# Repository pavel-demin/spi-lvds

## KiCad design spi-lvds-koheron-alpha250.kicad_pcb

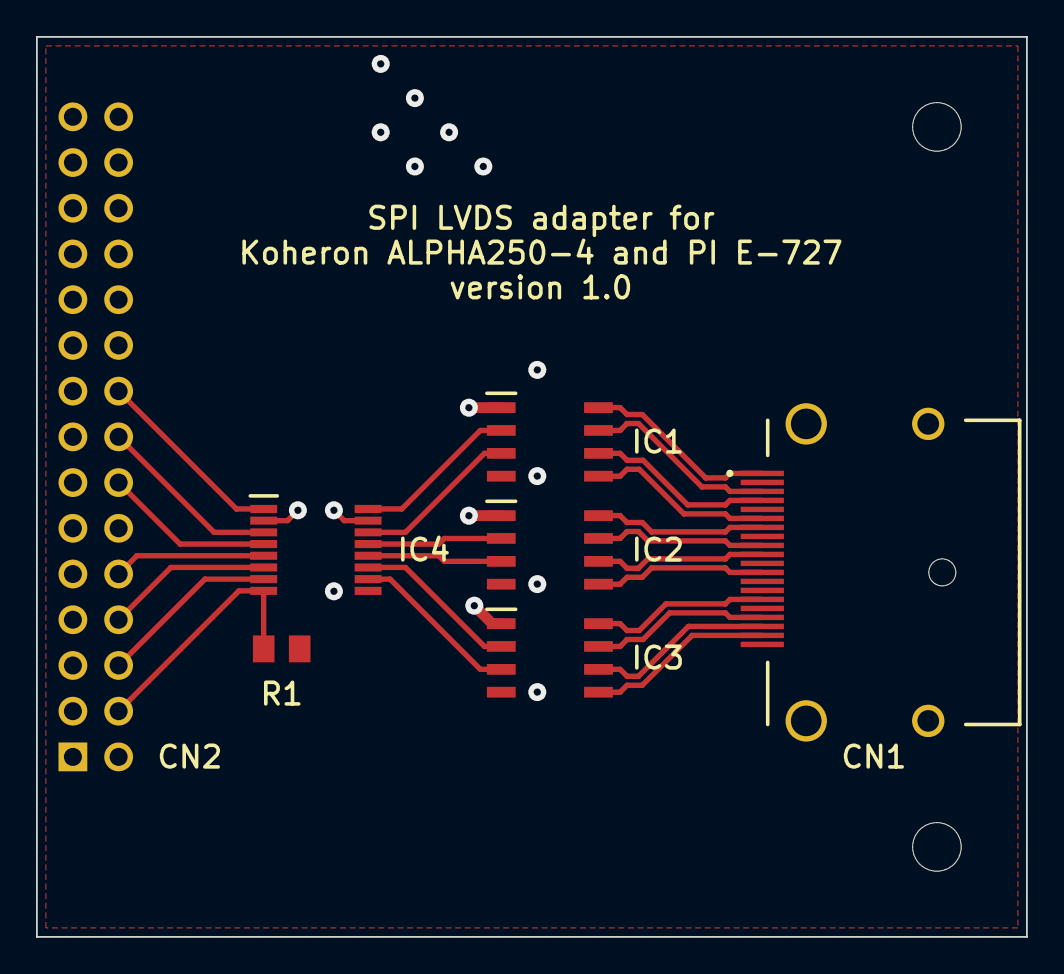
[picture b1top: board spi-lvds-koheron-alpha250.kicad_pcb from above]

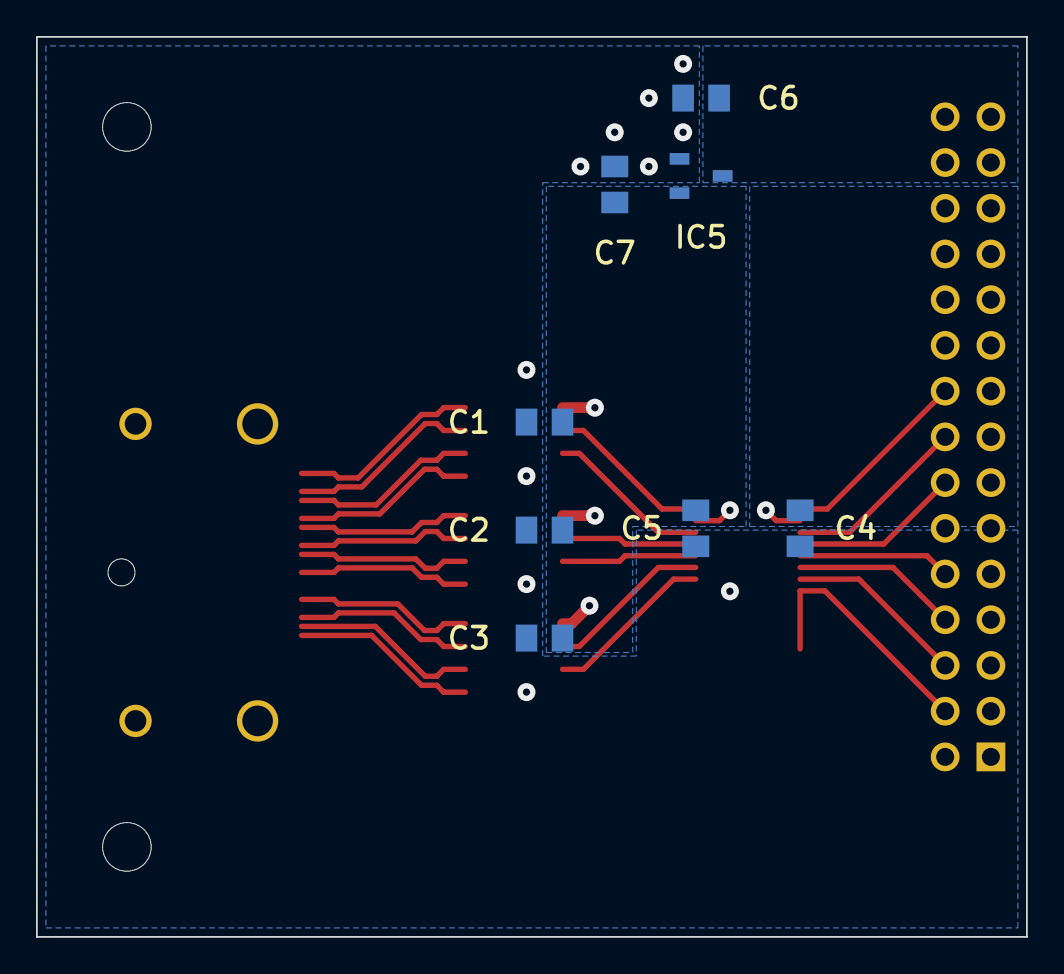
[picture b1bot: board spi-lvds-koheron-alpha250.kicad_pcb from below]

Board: 2 copper layers, 55.0 x 50.0 mm, 17 parts (8 on the bottom side), 29 nets.

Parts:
C1, C2, C3, C4, C5, C6, C7: 0805
CN1: 47272
CN2: 2x15
IC1, IC2, IC3: SOIC8
IC4: TSSOP16
IC5: SOT23
M1, M2: M25
R1: 0805

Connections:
1V8: C4.1, CN2.54, IC4.2
3V3: C1.1, C2.1, C3.1, C5.1, C7.1, IC1.1, IC2.1, IC3.1, IC4.15, IC5.2
5V: C6.1, CN2.57, IC5.3
CS: IC3.2, IC4.11
CS1V8: CN2.36, IC4.6
CS+: CN1.15, IC3.8
CS-: CN1.17, IC3.7
DCLK: IC2.3, IC4.12
DCLK1V8: CN2.38, IC4.5
DCLK+: CN1.10, IC2.6
DCLK-: CN1.12, IC2.5
GND: C1.2, C2.2, C3.2, C4.2, C5.2, C6.2, C7.2, CN1.2, CN1.5, CN1.8, CN1.11, CN1.13, CN1.14, CN1.16, CN1.MH1, CN1.MH2, CN1.MH3, CN1.MH4, CN2.29, CN2.30, CN2.39, CN2.40, CN2.49, CN2.50, CN2.55, IC1.4, IC2.4, IC3.4, IC4.9, IC5.1, R1.2
LDAT: IC3.3, IC4.10
LDAT1V8: CN2.34, IC4.7
LDAT+: CN1.18, IC3.6
LDAT-: CN1.19, IC3.5
MISO: IC2.2, IC4.13
MISO1V8: CN2.42, IC4.4
MISO+: CN1.7, IC2.8
MISO-: CN1.9, IC2.7
MOSI: IC1.3, IC4.14
MOSI1V8: CN2.44, IC4.3
MOSI+: CN1.4, IC1.6
MOSI-: CN1.6, IC1.5
OE1V8: CN2.32, IC4.8, R1.1
SCLK: IC1.2, IC4.16
SCLK1V8: CN2.46, IC4.1
SCLK+: CN1.1, IC1.8
SCLK-: CN1.3, IC1.7

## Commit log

2022-12-09 add attr to footprints
2022-12-09 improve filled zones
2022-12-09 replace roundrect with rect
2022-12-09 set dp width to 0.3 mm and dp gap to 0.2 mm
2022-12-09 set trace width to 0.6 mm
2022-12-09 increase via size
2022-12-09 add gnd traces
2022-12-13 improve GND and VCC
2024-02-06 add adapter for ALPHA250-4
2024-02-07 improve silkscreen line in SOIC8
2024-02-07 update PCB for Red Pitaya
2024-02-07 update PCB for Koheron ALPHA250-4
2024-02-09 improve PCB layout
2024-02-09 increase pin header pads hole size
2024-02-09 update pin header footprints in PCB files
2024-02-09 improve 0805 footprint
2024-02-09 reduce via diameter
2024-02-09 switch to kicad 7
2024-02-11 improve mounting holes
2024-02-11 connect DP shield to GND
